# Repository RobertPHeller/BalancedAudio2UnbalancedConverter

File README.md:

# Stereo Balanced Audio To Unbalanced Converter

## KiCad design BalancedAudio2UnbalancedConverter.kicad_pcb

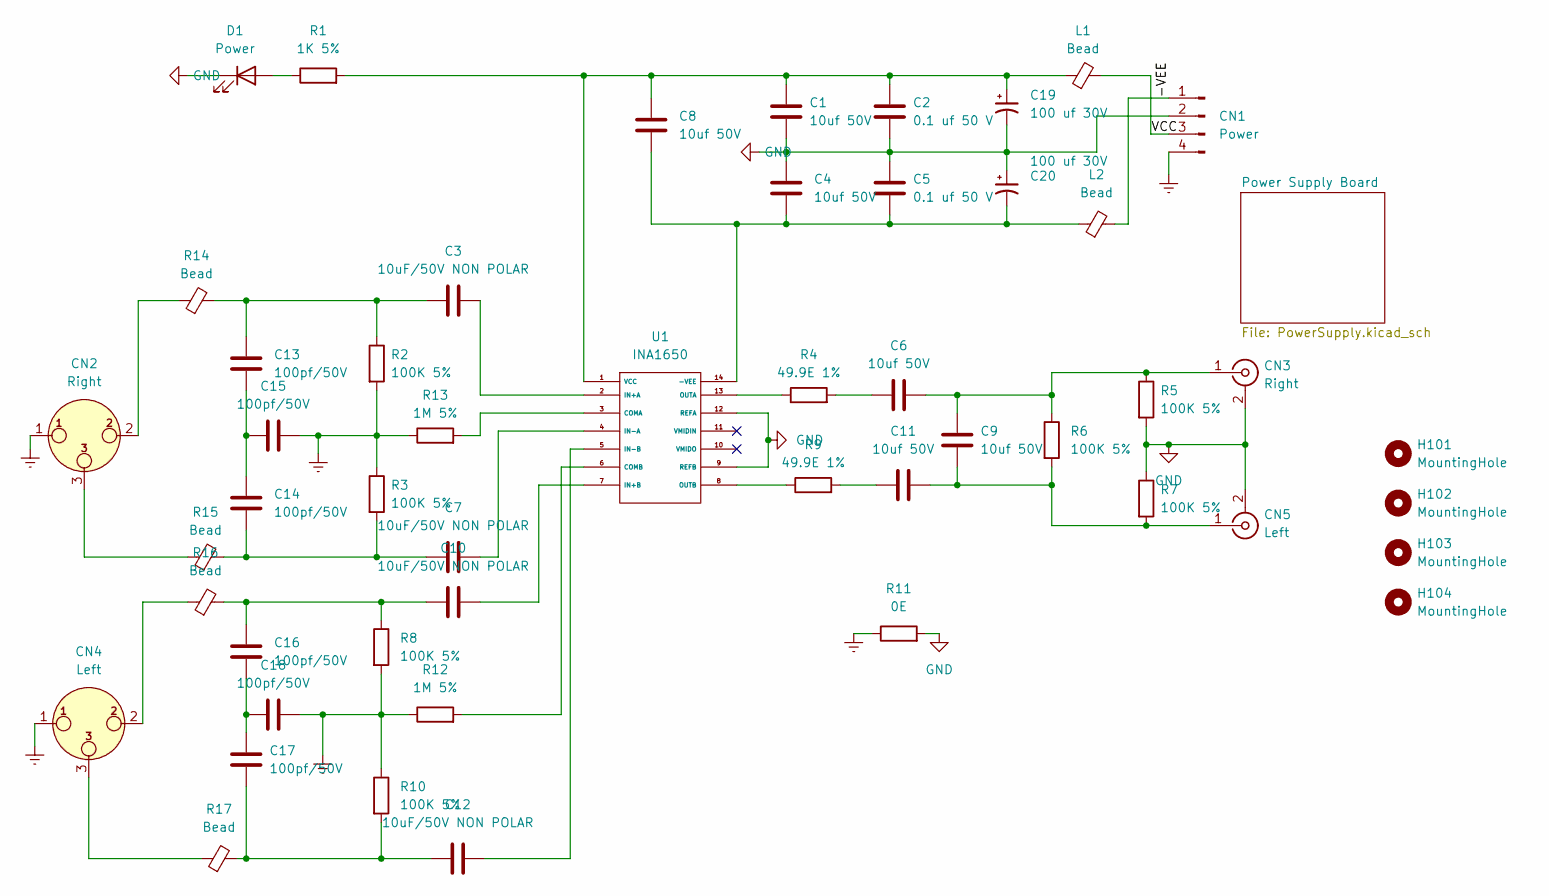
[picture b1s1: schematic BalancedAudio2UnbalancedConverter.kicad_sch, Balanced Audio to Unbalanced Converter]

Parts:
C1, C4, C6, C8, C9, C11: 10uf 50V; C_1206_3216Metric; Mouser Part Number 81-GRM31CD71H106KE1L
C2, C5: 0.1 uf 50 V; C_0805_2012Metric; Mouser Part Number 81-GCM21BR91H104MA7L
C3, C7, C10, C12: 10uF/50V NON POLAR; C_Radial_D8.0mm_H11.5mm_P3.50mm; Mouser Part Number 647-UES1H100MPM1TD
C13, C14, C15, C16, C17, C18: 100pf/50V; C_0805_2012Metric; Mouser Part Number 603-CC805JPNPO9BN101
C19, C20: 100 uf 30V; CP_Elec_8x10; Mouser Part Number 71-MAL214297007E3
CN1: Power; PinHeader_1x04_P2.54mm_Vertical
CN2: Right; Jack_XLR_Neutrik_NC3FAAH_Horizontal; Mouser Part Number 568-NC3FAAH-O
CN3: Right; RCJ011SMTTR; Mouser Part Number 490-RCJ-012-SMT-TR
CN4: Left; Jack_XLR_Neutrik_NC3FAAH_Horizontal; Mouser Part Number 568-NC3FAAH-O
CN5: Left; RCJ011SMTTR; Mouser Part Number 490-RCJ-013-SMT-TR
D1: Power; LED_0805_2012Metric; Mouser Part Number 859-LTST-C171KRKT
H101, H102, H103, H104: MountingHole; MountingHole_3.2mm_M3
L1, L2: Bead; R_0603_1608Metric; Mouser Part Number 810-MMZ1608R150ATA00
R1: 1K 5%; R_0805_2012Metric; Mouser Part Number 603-RC0805JR-131KL
R2, R3, R5, R6, R7, R8, R10: 100K 5%; R_0805_2012Metric; Mouser Part Number 603-AC0805JR-07100KL
R4, R9: 49.9E 1%; R_0805_2012Metric; Mouser Part Number 71-CRCW0805-49.9-E3
R11: 0E; R_0805_2012Metric; Mouser Part Number 603-RC0805JR-070RL
R12, R13: 1M 5%; R_0805_2012Metric; Mouser Part Number 603-RV0805JR-071ML
R14, R15, R16, R17: Bead; R_0603_1608Metric; Mouser Part Number 810-MMZ1608R150ATA00
U1: INA1650; TSSOP-14_4.4x5mm_P0.65mm; Mouser Part Number 595-INA1650IPWR

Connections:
/-VEE: CN1.1, L2.2
/VCC: CN1.3, L1.2
Earth: C15.2, C18.2, CN1.4, CN2.1, CN4.1, R2.2, R3.1, R8.2, R10.1, R11.1, R12.1, R13.1; also elsewhere on the board
GND: C1.2, C2.2, C4.1, C5.1, C19.2, C20.1, CN1.2, CN3.2 (Ext), CN5.2 (Ext), D1.1 (K), R5.2, R7.1, R11.2, U1.9 (REFB), U1.12 (REFA); also elsewhere on the board
unnamed: C1.1, C2.1, C8.1, C19.1, L1.1, R1.2, U1.1 (VCC)
unnamed: C3.2, U1.2 (IN+A)
unnamed: C6.1, R4.2
unnamed: C6.2, C9.1, CN3.1 (In), R5.1, R6.1
unnamed: C7.2, U1.4 (IN-A)
unnamed: C10.1, C16.1, R8.1, R16.2
unnamed: C10.2, U1.7 (IN+B)
unnamed: C11.1, R9.2
unnamed: C9.2, C11.2, CN5.1 (In), R6.2, R7.2
unnamed: C12.1, C17.2, R10.2, R17.2
unnamed: C12.2, U1.5 (IN-B)
unnamed: C3.1, C13.1, R2.1, R14.2
unnamed: C13.2, C14.1, C15.1
unnamed: C7.1, C14.2, R3.2, R15.2
unnamed: C16.2, C17.1, C18.1
unnamed: C4.2, C5.2, C8.2, C20.2, L2.1, U1.14 (-VEE)
unnamed: CN2.2, R14.1
unnamed: CN2.3, R15.1
unnamed: D1.2 (A), R1.1
unnamed: R4.1, U1.13 (OUTA)
unnamed: R9.1, U1.8 (OUTB)
unnamed: R12.2, U1.6 (COMB)
unnamed: R13.2, U1.3 (COMA)
unnamed: CN4.2, R16.1
unnamed: CN4.3, R17.1

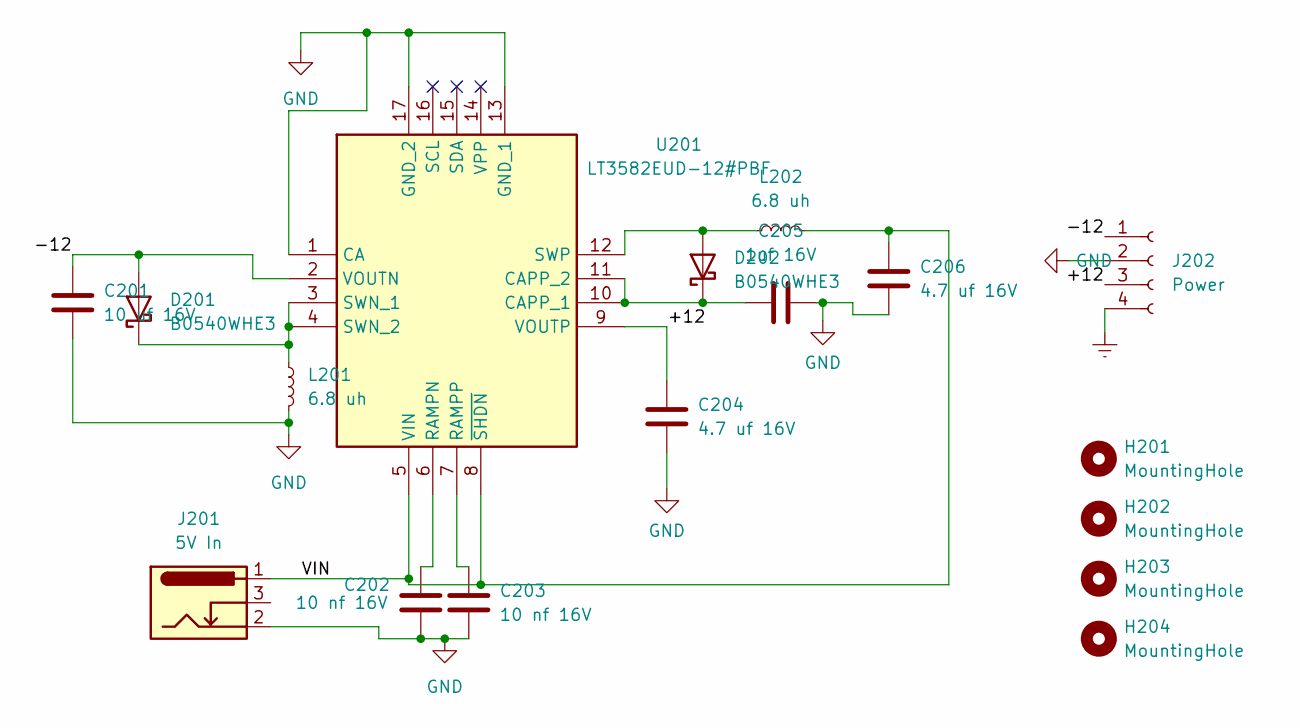
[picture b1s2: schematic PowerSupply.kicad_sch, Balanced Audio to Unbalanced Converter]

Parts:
C201: 10 uf 16V; C_0603_1608Metric; Mouser Part Number 81-GRM188C81C106MA3J
C202, C203: 10 nf 16V; C_0603_1608Metric; Mouser Part Number 603-CC603KRX7R7BB103
C204, C206: 4.7 uf 16V; C_0603_1608Metric; Mouser Part Number 81-GRT188R61C475KE3D
C205: 1uf 16V; C_0603_1608Metric; Mouser Part Number 81-GRM188R61C105KA2J
D201, D202: B0540WHE3; D_SOD-123; Mouser Part Number 833-B0540WHE3-TP
H201, H202, H203, H204: MountingHole; MountingHole_3.2mm_M3
J201: 5V In; KLDX0202AC; Mouser Part Number 806-KLDX-0202-AC
J202: Power; PinSocket_1x04_P2.54mm_Vertical
L201, L202: 6.8 uh; L_0603_1608Metric; Mouser Part Number 652-CWF1610A-6R8K
U201: LT3582EUD-12#PBF; QFN50P300X300X80-17N-D; Mouser Part Number 584-LT3582EUD-12#PBF

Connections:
/Power Supply Board/+12: C204.1, J202.3, U201.9 (VOUTP)
/Power Supply Board/-12: C201.1, D201.2 (A), J202.1, U201.2 (VOUTN)
/Power Supply Board/VIN: C206.1, J201.1, L202.2, U201.5 (VIN), U201.8 (~SHDN)
Earth: J202.4; also elsewhere on the board
GND: C201.2, C202.2, C203.2, C204.2, C205.2, C206.2, J201.2, J202.2, L201.2, U201.1 (CA), U201.13 (GND_1), U201.17 (GND_2); also elsewhere on the board
unnamed: C202.1, U201.6 (RAMPN)
unnamed: C203.1, U201.7 (RAMPP)
unnamed: C205.1, D202.1 (K), U201.10 (CAPP_1), U201.11 (CAPP_2)
unnamed: D201.1 (K), L201.1, U201.3 (SWN_1), U201.4 (SWN_2)
unnamed: D202.2 (A), L202.1, U201.12 (SWP)

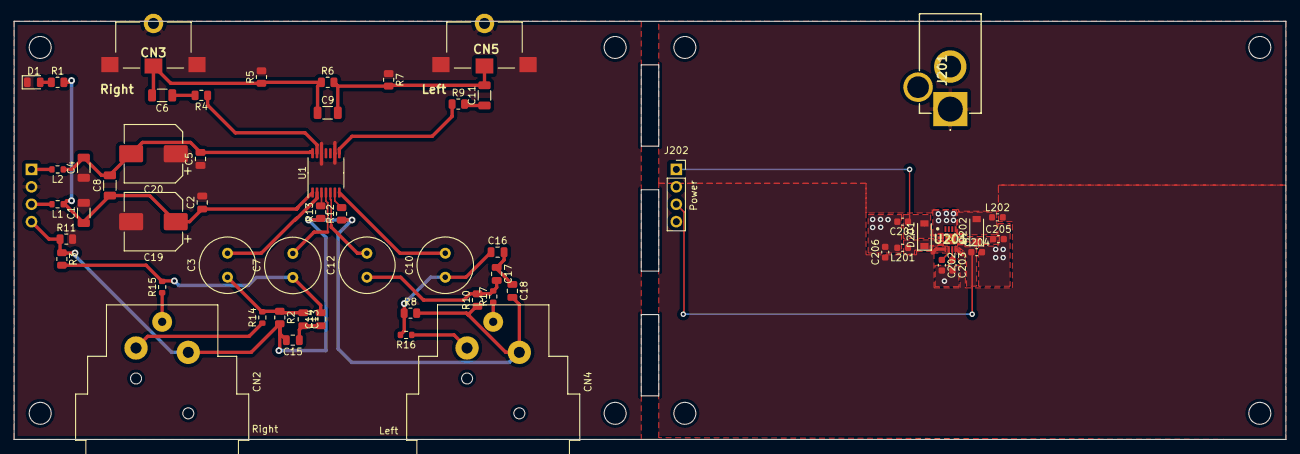
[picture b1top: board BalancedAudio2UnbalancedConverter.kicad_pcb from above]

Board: 2 copper layers, 185.4 x 61.0 mm, 67 parts (1 on the bottom side), 37 nets.
